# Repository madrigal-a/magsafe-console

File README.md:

# MagSafe Console

Consola retro open source del tamaño de una tarjeta que se pega por MagSafe a la parte de atrás del celular.

**Estado: en diseño.** Todavía no hay hardware probado.

## Qué es

- Emula NES, Game Boy, Game Boy Color, Master System y Game Gear con [Retro-Go](https://github.com/ducalex/retro-go).
- ESP32-S3 con 8 MB de PSRAM.
- Pantalla IPS a color de 2.4", 320×240.
- Objetivo de tamaño: aprox. 64 × 98 mm y de 8 a 9 mm de grosor, con anillo de imanes MagSafe en la tapa trasera.
- Batería LiPo de 800 a 1000 mAh, con objetivo de 5 a 6 horas de juego.
- PCB fabricada en JLCPCB y armada a mano con piezas de LCSC; carcasa impresa en 3D.

Game Boy Advance queda fuera de esta versión: la ESP32-S3 no lo corre bien.

## Contenido

| Carpeta | Contenido |
|---|---|
| [docs/](docs/) | Guía de conexiones del prototipo y plano de acomodo |
| [firmware/](firmware/) | Target de Retro-Go para esta consola |
| [hardware/](hardware/) | Esquemático y PCB en KiCad, piezas y revisión de huellas |
| [PENDIENTES.md](PENDIENTES.md) | Lista de lo que falta |

## Plan

1. Prototipo en protoboard con placa de desarrollo.
2. Esquemático y PCB en KiCad.
3. Primer pedido a JLCPCB.
4. Carcasa impresa en 3D.

## Licencia

Por definir. El target de firmware deriva de Retro-Go y es GPLv2. Este repo no incluye ROMs.

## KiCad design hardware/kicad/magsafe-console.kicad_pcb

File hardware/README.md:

# Hardware

Proyecto de KiCad y, más adelante, los archivos de fabricación para JLCPCB.

| Archivo | Contenido |
|---|---|
| [kicad/magsafe-console.kicad_pro](kicad/magsafe-console.kicad_pro) | Proyecto. Abrir este en KiCad (formato 9, compatible con 10) |
| [kicad/magsafe-console.kicad_sch](kicad/magsafe-console.kicad_sch) | Esquemático v0.1 |
| [kicad/magsafe-console.kicad_pcb](kicad/magsafe-console.kicad_pcb) | PCB: contorno y colocación inicial, sin pistas |
| [esquematico.pdf](esquematico.pdf) | El esquemático en PDF |
| [circuito.md](circuito.md) | Explicación del circuito por bloques |
| [piezas.md](piezas.md) | Piezas verificadas en el catálogo de JLCPCB |
| [revision-huellas.md](revision-huellas.md) | Revisión de las huellas contra las hojas de datos |
| [pcb.md](pcb.md) | Estado de la PCB y dónde quedó cada pieza |
| [kicad/lib/](kicad/lib/) | Símbolos, huellas y modelos 3D de piezas que no trae KiCad |

## Estado del esquemático

- Pasa la revisión eléctrica (ERC) de KiCad 9 sin errores. Queda un aviso inofensivo en el pad térmico del amplificador.
- **Sin probar en hardware.**
- Las conexiones se hacen con etiquetas de red en vez de cables largos: dos pines con la misma etiqueta están conectados.
- **Provisional:** el conector de la pantalla (J3) y la resistencia de la luz de fondo (R13).
- **Sin huella asignada todavía:** solo el conector de la pantalla.
- Las huellas ya se compararon contra las hojas de datos: ver [revision-huellas.md](revision-huellas.md).
- La PCB está iniciada: ver [pcb.md](pcb.md).

**Pendiente:** elegir el modelo exacto de pantalla. Su conector define parte del esquemático.

## Bloques del circuito

| Bloque | Pieza prevista |
|---|---|
| Cerebro | ESP32-S3-WROOM-1-N16R8 |
| Pantalla | IPS 2.4" 320×240 ST7789, conector FPC |
| Almacenamiento | Ranura microSD |
| Audio | MAX98357A + bocina de 8 Ω |
| Energía | USB-C, cargador de litio, regulador a 3.3 V, LiPo de 800 a 1000 mAh |
| Controles | Cruceta, A, B, Start, Select, Menu, Option, L, R |

La asignación de pines está en [docs/prototipo-conexiones.md](../docs/prototipo-conexiones.md).

El diseño por bloques, con piezas y conexiones, está en [circuito.md](circuito.md).

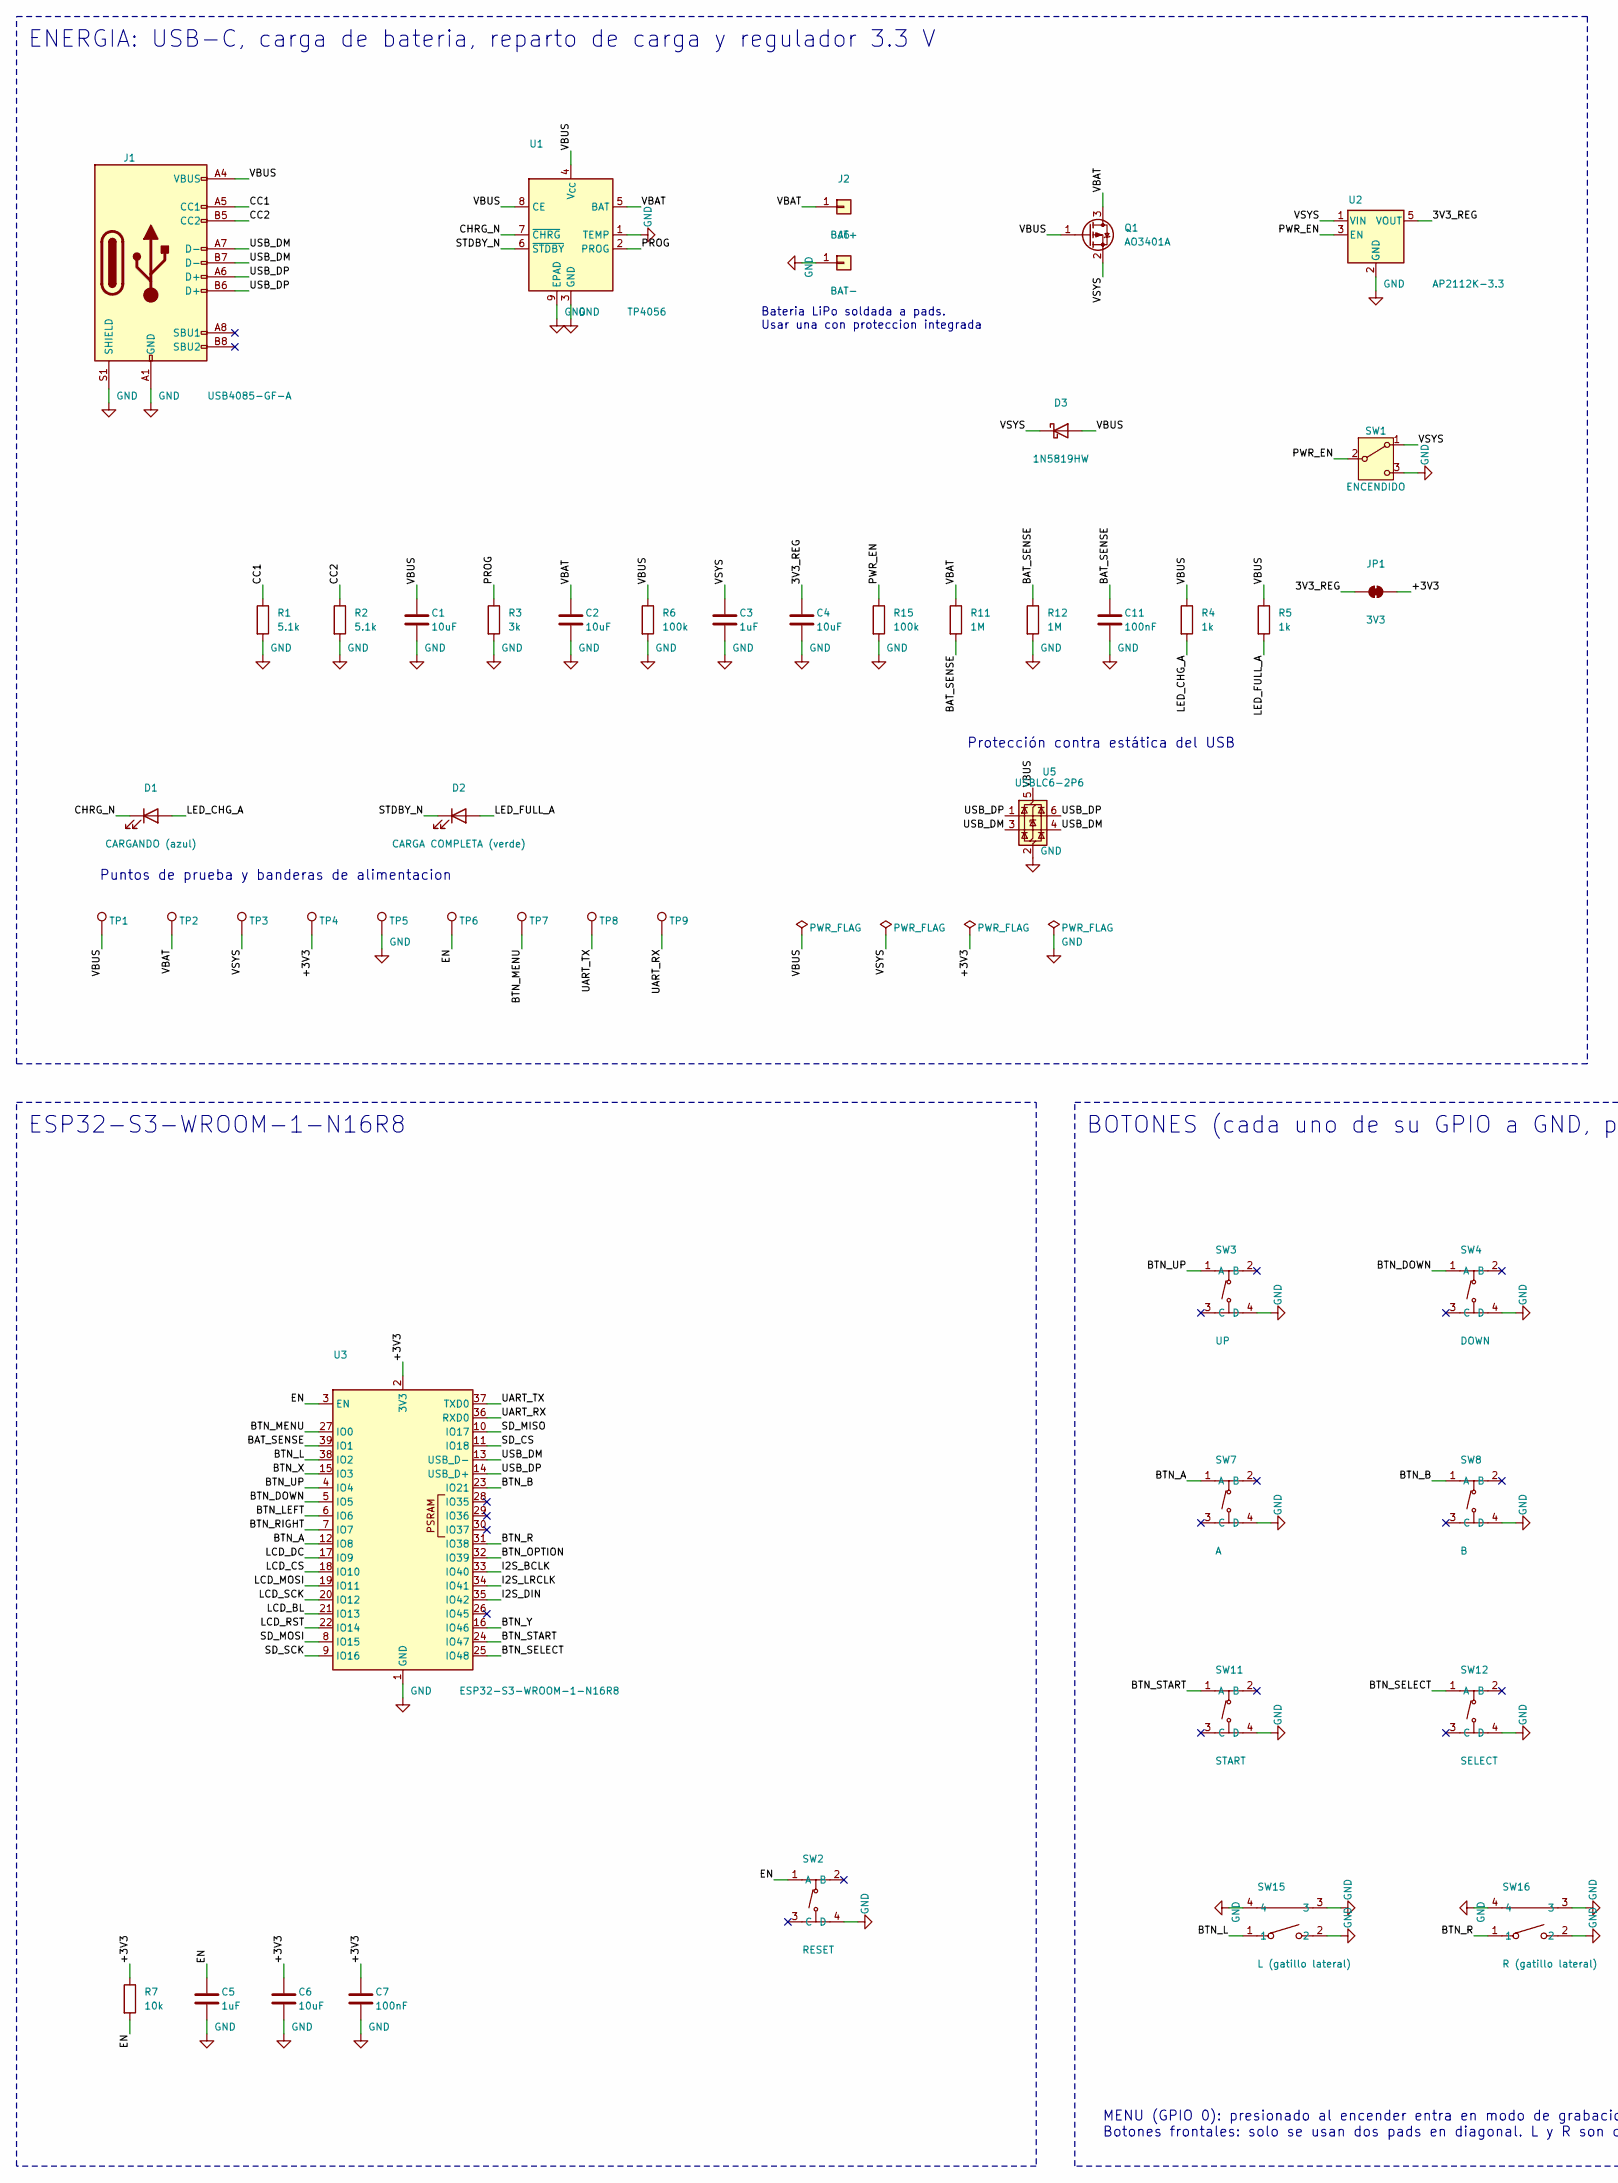
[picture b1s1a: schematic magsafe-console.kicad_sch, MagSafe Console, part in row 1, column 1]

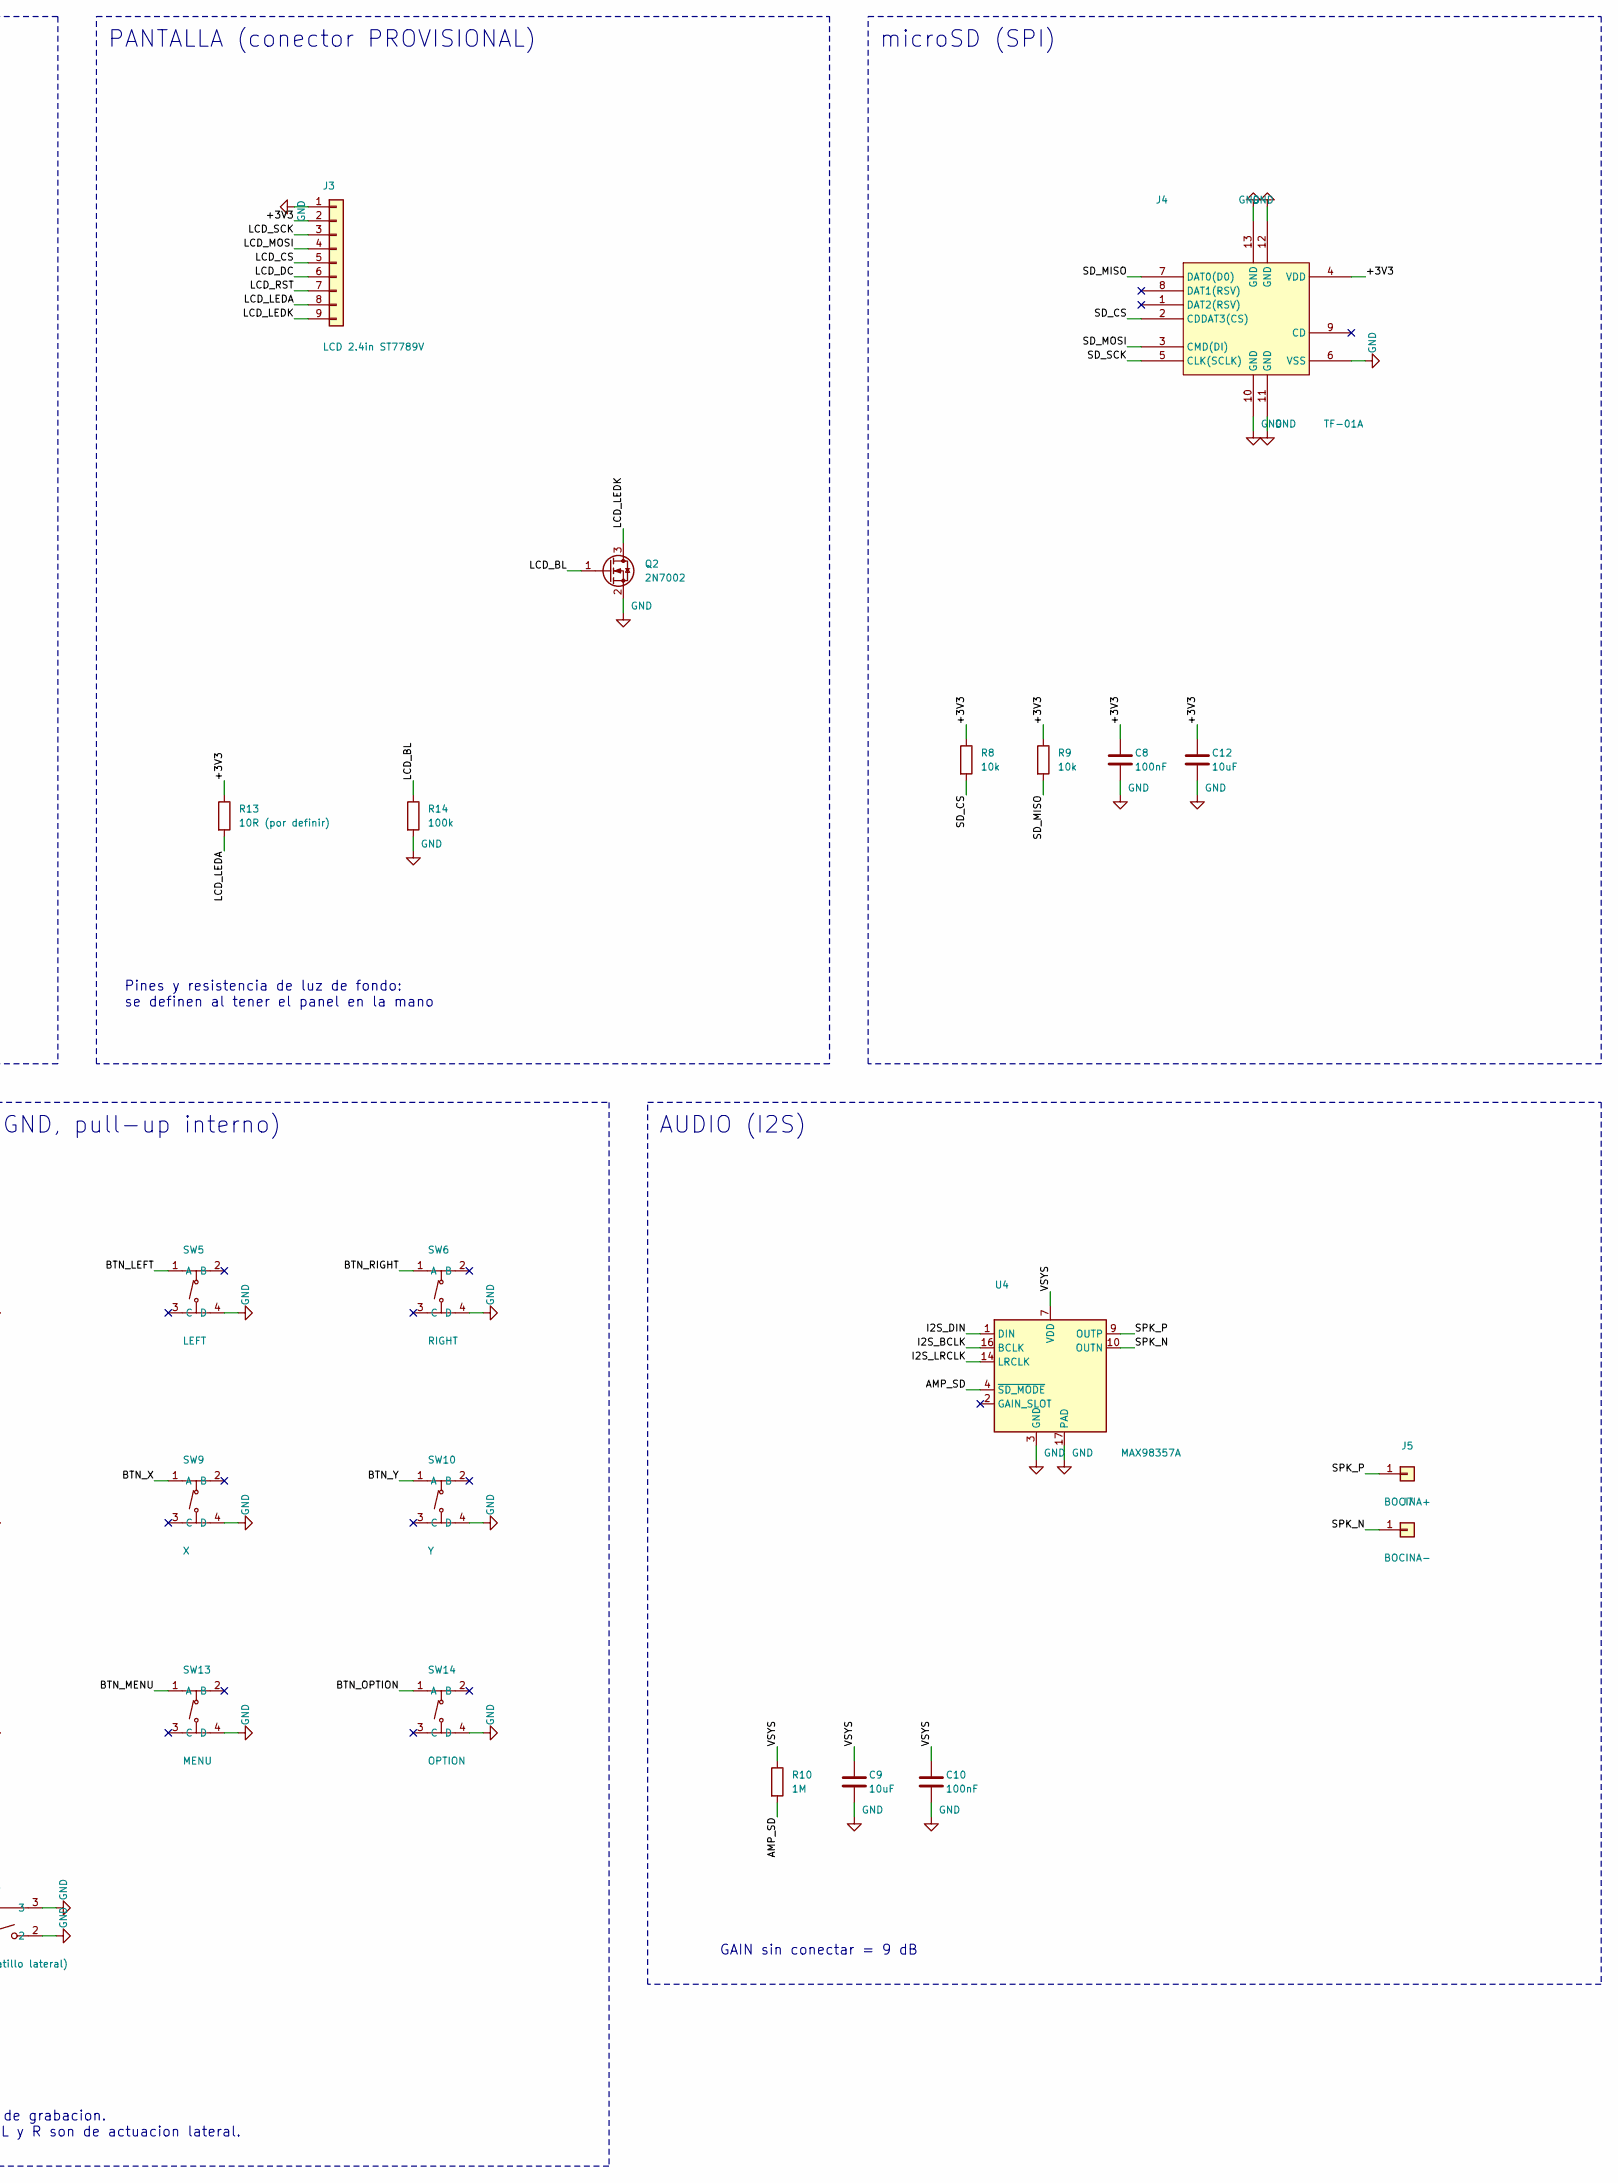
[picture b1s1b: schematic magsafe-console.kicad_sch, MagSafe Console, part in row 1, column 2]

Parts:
C1, C2, C4, C6, C9, C12: 10uF; C_0805_2012Metric
C3, C5: 1uF; C_0603_1608Metric; LCSC C15849
C7, C8, C10, C11: 100nF; C_0603_1608Metric; LCSC C14663
D1: CARGANDO (azul); LED_0603_1608Metric
D2: CARGA COMPLETA (verde); LED_0603_1608Metric
D3: 1N5819HW; D_SOD-123; LCSC C82544
J1: USB4085-GF-A; USB_C_Receptacle_GCT_USB4085
J2: BAT+; SolderWirePad_1x01_SMD_1.5x3mm
J3: LCD 2.4in ST7789V
J4: TF-01A; TF-SMD_TF-01A; LCSC C91145
J5: BOCINA+; SolderWirePad_1x01_SMD_1x2mm
J6: BAT-; SolderWirePad_1x01_SMD_1.5x3mm
J7: BOCINA-; SolderWirePad_1x01_SMD_1x2mm
JP1: 3V3; SolderJumper-2_P1.3mm_Bridged_RoundedPad1.0x1.5mm
Q1: AO3401A; SOT-23; LCSC C15127
Q2: 2N7002; SOT-23; LCSC C8545
R1, R2: 5.1k; R_0603_1608Metric; LCSC C23186
R3: 3k; R_0603_1608Metric; LCSC C4211
R4, R5: 1k; R_0603_1608Metric; LCSC C21190
R6, R14, R15: 100k; R_0603_1608Metric; LCSC C25803
R7, R8, R9: 10k; R_0603_1608Metric; LCSC C25804
R10, R11, R12: 1M; R_0603_1608Metric; LCSC C22935
R13: 10R (por definir); R_0603_1608Metric; LCSC C22859
SW1: ENCENDIDO; SW_SPDT_Shouhan_MSK12C02; LCSC C431540
SW2: RESET; SW-SMD_4P-L5.1-W5.1-P3.70-LS6.5-TL_H1.5; LCSC C318884
SW3: UP; SW-SMD_4P-L5.1-W5.1-P3.70-LS6.5-TL_H1.5; LCSC C318884
SW4: DOWN; SW-SMD_4P-L5.1-W5.1-P3.70-LS6.5-TL_H1.5; LCSC C318884
SW5: LEFT; SW-SMD_4P-L5.1-W5.1-P3.70-LS6.5-TL_H1.5; LCSC C318884
SW6: RIGHT; SW-SMD_4P-L5.1-W5.1-P3.70-LS6.5-TL_H1.5; LCSC C318884
SW7: A; SW-SMD_4P-L5.1-W5.1-P3.70-LS6.5-TL_H1.5; LCSC C318884
SW8: B; SW-SMD_4P-L5.1-W5.1-P3.70-LS6.5-TL_H1.5; LCSC C318884
SW9: X; SW-SMD_4P-L5.1-W5.1-P3.70-LS6.5-TL_H1.5; LCSC C318884
SW10: Y; SW-SMD_4P-L5.1-W5.1-P3.70-LS6.5-TL_H1.5; LCSC C318884
SW11: START; SW-SMD_4P-L5.1-W5.1-P3.70-LS6.5-TL_H1.5; LCSC C318884
SW12: SELECT; SW-SMD_4P-L5.1-W5.1-P3.70-LS6.5-TL_H1.5; LCSC C318884
SW13: MENU; SW-SMD_4P-L5.1-W5.1-P3.70-LS6.5-TL_H1.5; LCSC C318884
SW14: OPTION; SW-SMD_4P-L5.1-W5.1-P3.70-LS6.5-TL_H1.5; LCSC C318884
SW15: L (gatillo lateral); SW-SMD_2P-TS24CA; LCSC C393942
SW16: R (gatillo lateral); SW-SMD_2P-TS24CA; LCSC C393942
TP1: VBUS; TestPoint_Pad_D1.0mm
TP2: VBAT; TestPoint_Pad_D1.0mm
TP3: VSYS; TestPoint_Pad_D1.0mm
TP4: +3V3; TestPoint_Pad_D1.0mm
TP5: GND; TestPoint_Pad_D1.0mm
TP6: EN; TestPoint_Pad_D1.0mm
TP7: BTN_MENU; TestPoint_Pad_D1.0mm
TP8: UART_TX; TestPoint_Pad_D1.0mm
TP9: UART_RX; TestPoint_Pad_D1.0mm
U1: TP4056; SOIC-8-1EP_3.9x4.9mm_P1.27mm_EP2.41x3.3mm_ThermalVias; LCSC C16581
U2: AP2112K-3.3; SOT-23-5; LCSC C51118
U3: ESP32-S3-WROOM-1-N16R8; ESP32-S3-WROOM-1_KeepoutReducido; LCSC C2913202
U4: MAX98357A; TQFN-16-1EP_3x3mm_P0.5mm_EP1.23x1.23mm; LCSC C910544
U5: USBLC6-2P6; SOT-666; LCSC C15999

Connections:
/3V3_REG: C4.1, JP1.1 (A), U2.5 (VOUT)
/+3V3: C6.1, C7.1, C8.1, C12.1, J3.2, J4.4 (VDD), JP1.2 (B), R7.1, R8.1, R9.1, R13.1, TP4.1, U3.2 (3V3)
/AMP_SD: R10.2, U4.4 (~SD_MODE)
/BAT_SENSE: C11.1, R11.2, R12.1, U3.39 (IO1)
/BTN_A: SW7.1 (A), U3.12 (IO8)
/BTN_B: SW8.1 (A), U3.23 (IO21)
/BTN_DOWN: SW4.1 (A), U3.5 (IO5)
/BTN_L: SW15.1, U3.38 (IO2)
/BTN_LEFT: SW5.1 (A), U3.6 (IO6)
/BTN_MENU: SW13.1 (A), TP7.1, U3.27 (IO0)
/BTN_OPTION: SW14.1 (A), U3.32 (IO39)
/BTN_R: SW16.1, U3.31 (IO38)
/BTN_RIGHT: SW6.1 (A), U3.7 (IO7)
/BTN_SELECT: SW12.1 (A), U3.25 (IO48)
/BTN_START: SW11.1 (A), U3.24 (IO47)
/BTN_UP: SW3.1 (A), U3.4 (IO4)
/BTN_X: SW9.1 (A), U3.15 (IO3)
/BTN_Y: SW10.1 (A), U3.16 (IO46)
/CC1: J1.A5 (CC1), R1.1
/CC2: J1.B5 (CC2), R2.1
/CHRG_N: D1.1 (K), U1.7 (~CHRG)
/EN: C5.1, R7.2, SW2.1 (A), TP6.1, U3.3 (EN)
/I2S_BCLK: U3.33 (IO40), U4.16 (BCLK)
/I2S_DIN: U3.35 (IO42), U4.1 (DIN)
/I2S_LRCLK: U3.34 (IO41), U4.14 (LRCLK)
/LCD_BL: Q2.1 (G), R14.1, U3.21 (IO13)
/LCD_CS: J3.5, U3.18 (IO10)
/LCD_DC: J3.6, U3.17 (IO9)
/LCD_LEDA: J3.8, R13.2
/LCD_LEDK: J3.9, Q2.3 (D)
/LCD_MOSI: J3.4, U3.19 (IO11)
/LCD_RST: J3.7, U3.22 (IO14)
/LCD_SCK: J3.3, U3.20 (IO12)
/LED_CHG_A: D1.2 (A), R4.2
/LED_FULL_A: D2.2 (A), R5.2
/PROG: R3.1, U1.2 (PROG)
/PWR_EN: R15.1, SW1.2 (B), U2.3 (EN)
/SD_CS: J4.2 (CDDAT3(CS)), R8.2, U3.11 (IO18)
/SD_MISO: J4.7 (DAT0(D0)), R9.2, U3.10 (IO17)
/SD_MOSI: J4.3 (CMD(DI)), U3.8 (IO15)
/SD_SCK: J4.5 (CLK(SCLK)), U3.9 (IO16)
/SPK_N: J7.1, U4.10 (OUTN)
/SPK_P: J5.1, U4.9 (OUTP)
/STDBY_N: D2.1 (K), U1.6 (~STDBY)
/UART_RX: TP9.1, U3.36 (RXD0)
/UART_TX: TP8.1, U3.37 (TXD0)
/USB_DM: J1.A7 (D-), J1.B7 (D-), U3.13 (USB_D-), U5.3 (I/O2), U5.4 (I/O2)
/USB_DP: J1.A6 (D+), J1.B6 (D+), U3.14 (USB_D+), U5.1 (I/O1), U5.6 (I/O1)
/VBAT: C2.1, J2.1, Q1.3 (D), R11.1, TP2.1, U1.5 (BAT)
/VBUS: C1.1, D3.2 (A), J1.A4 (VBUS), J1.A9 (VBUS), J1.B4 (VBUS), J1.B9 (VBUS), Q1.1 (G), R4.1, R5.1, R6.1, TP1.1, U1.4 (V_{CC}), U1.8 (CE), U5.5 (VBUS)
/VSYS: C3.1, C9.1, C10.1, D3.1 (K), Q1.2 (S), R10.1, SW1.1 (A), TP3.1, U2.1 (VIN), U4.7 (VDD), U4.8 (VDD)
GND: C1.2, C2.2, C3.2, C4.2, C5.2, C6.2, C7.2, C8.2, C9.2, C10.2, C11.2, C12.2, J1.A1 (GND), J1.A12 (GND), J1.B1 (GND), J1.B12 (GND), J1.S1 (SHIELD), J3.1, J4.6 (VSS), J4.10 (GND), J4.11 (GND), J4.12 (GND), J4.13 (GND), J6.1, Q2.2 (S), R1.2, R2.2, R3.2, R6.2, R12.2, R14.2, R15.2, SW1.3 (C), SW2.4 (D), SW3.4 (D), SW4.4 (D), SW5.4 (D), SW6.4 (D), SW7.4 (D), SW8.4 (D), SW9.4 (D), SW10.4 (D), SW11.4 (D), SW12.4 (D), SW13.4 (D), SW14.4 (D), SW15.2, SW15.3, SW15.4, SW16.2, SW16.3, SW16.4, TP5.1, U1.1 (TEMP), U1.3 (GND), U1.9 (EPAD), U2.2 (GND), U3.1 (GND), U3.40 (GND), U3.41 (GND), U4.3 (GND), U4.11 (GND), U4.15 (GND), U4.17 (PAD), U5.2 (GND)

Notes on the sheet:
ENERGIA: USB-C, carga de bateria, reparto de carga y regulador 3.3 V
Bateria LiPo soldada a pads. Usar una con proteccion integrada
Puntos de prueba y banderas de alimentacion
ESP32-S3-WROOM-1-N16R8
BOTONES (cada uno de su GPIO a GND, pull-up interno)
MENU (GPIO 0): presionado al encender entra en modo de grabacion. Botones frontales: solo se usan dos pads en diagonal. L y R son de actuacion lateral.
PANTALLA (conector PROVISIONAL)
Pines y resistencia de luz de fondo: se definen al tener el panel en la mano
microSD (SPI)
AUDIO (I2S)
GAIN sin conectar = 9 dB
Protección contra estática del USB

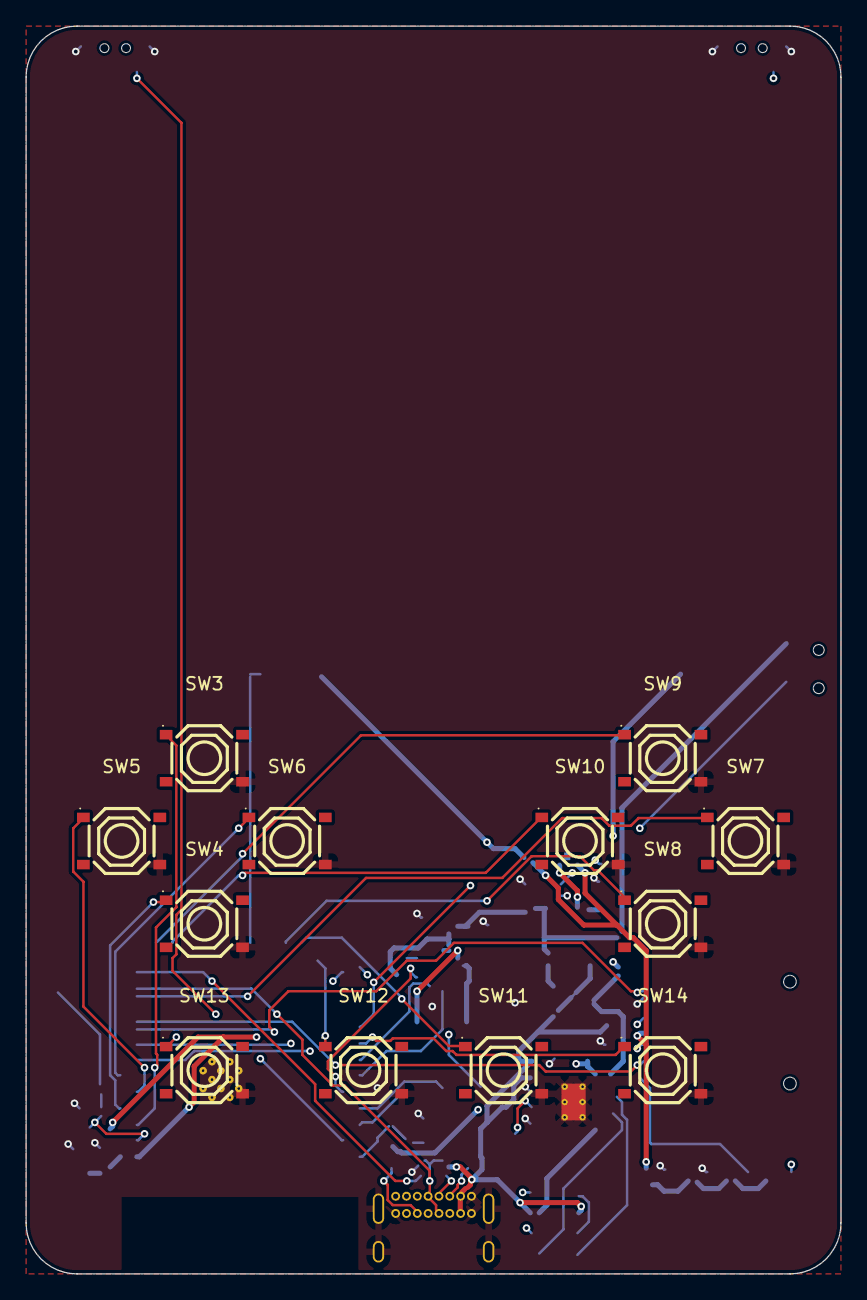
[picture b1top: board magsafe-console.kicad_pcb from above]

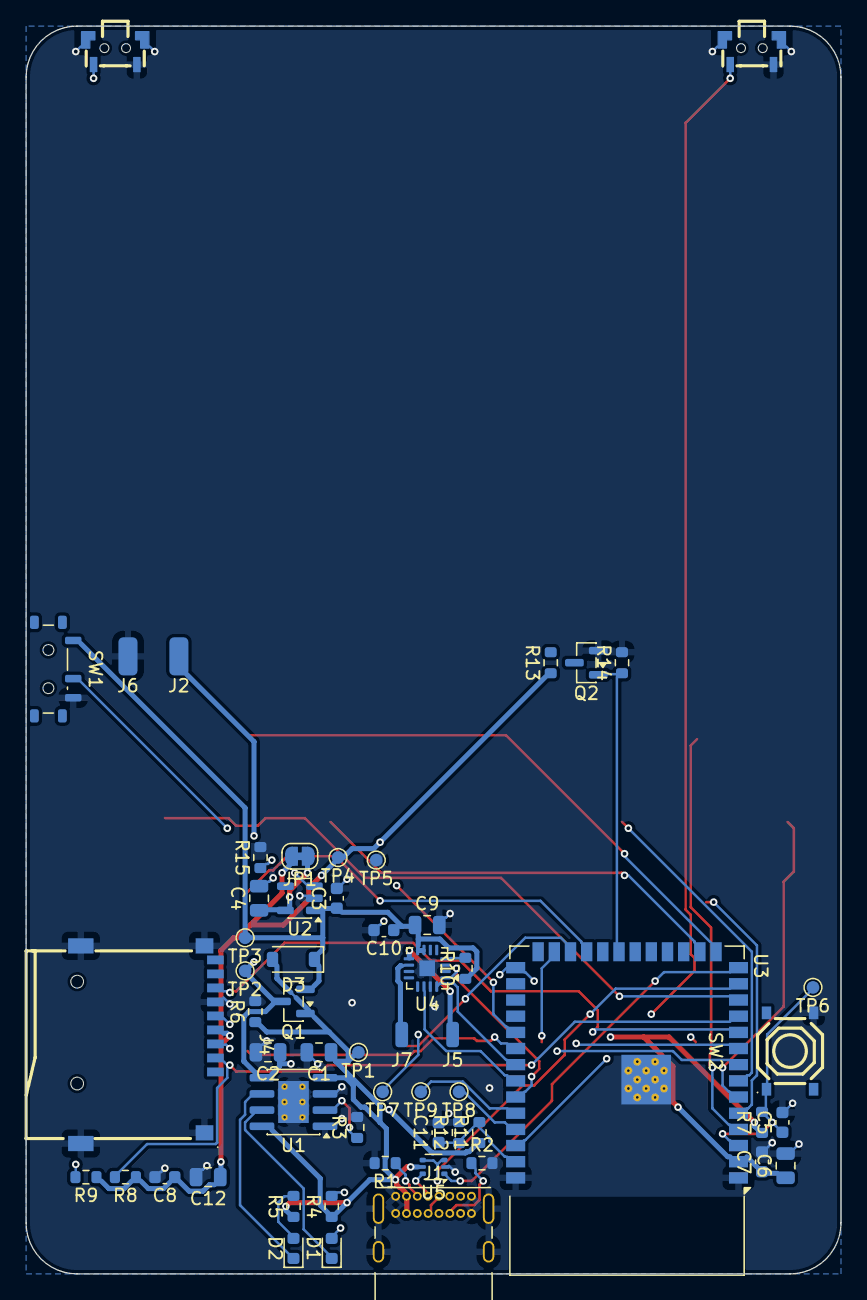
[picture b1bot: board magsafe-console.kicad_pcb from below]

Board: 4 copper layers, 64.0 x 98.0 mm, 69 parts (57 on the bottom side), 45 nets.
